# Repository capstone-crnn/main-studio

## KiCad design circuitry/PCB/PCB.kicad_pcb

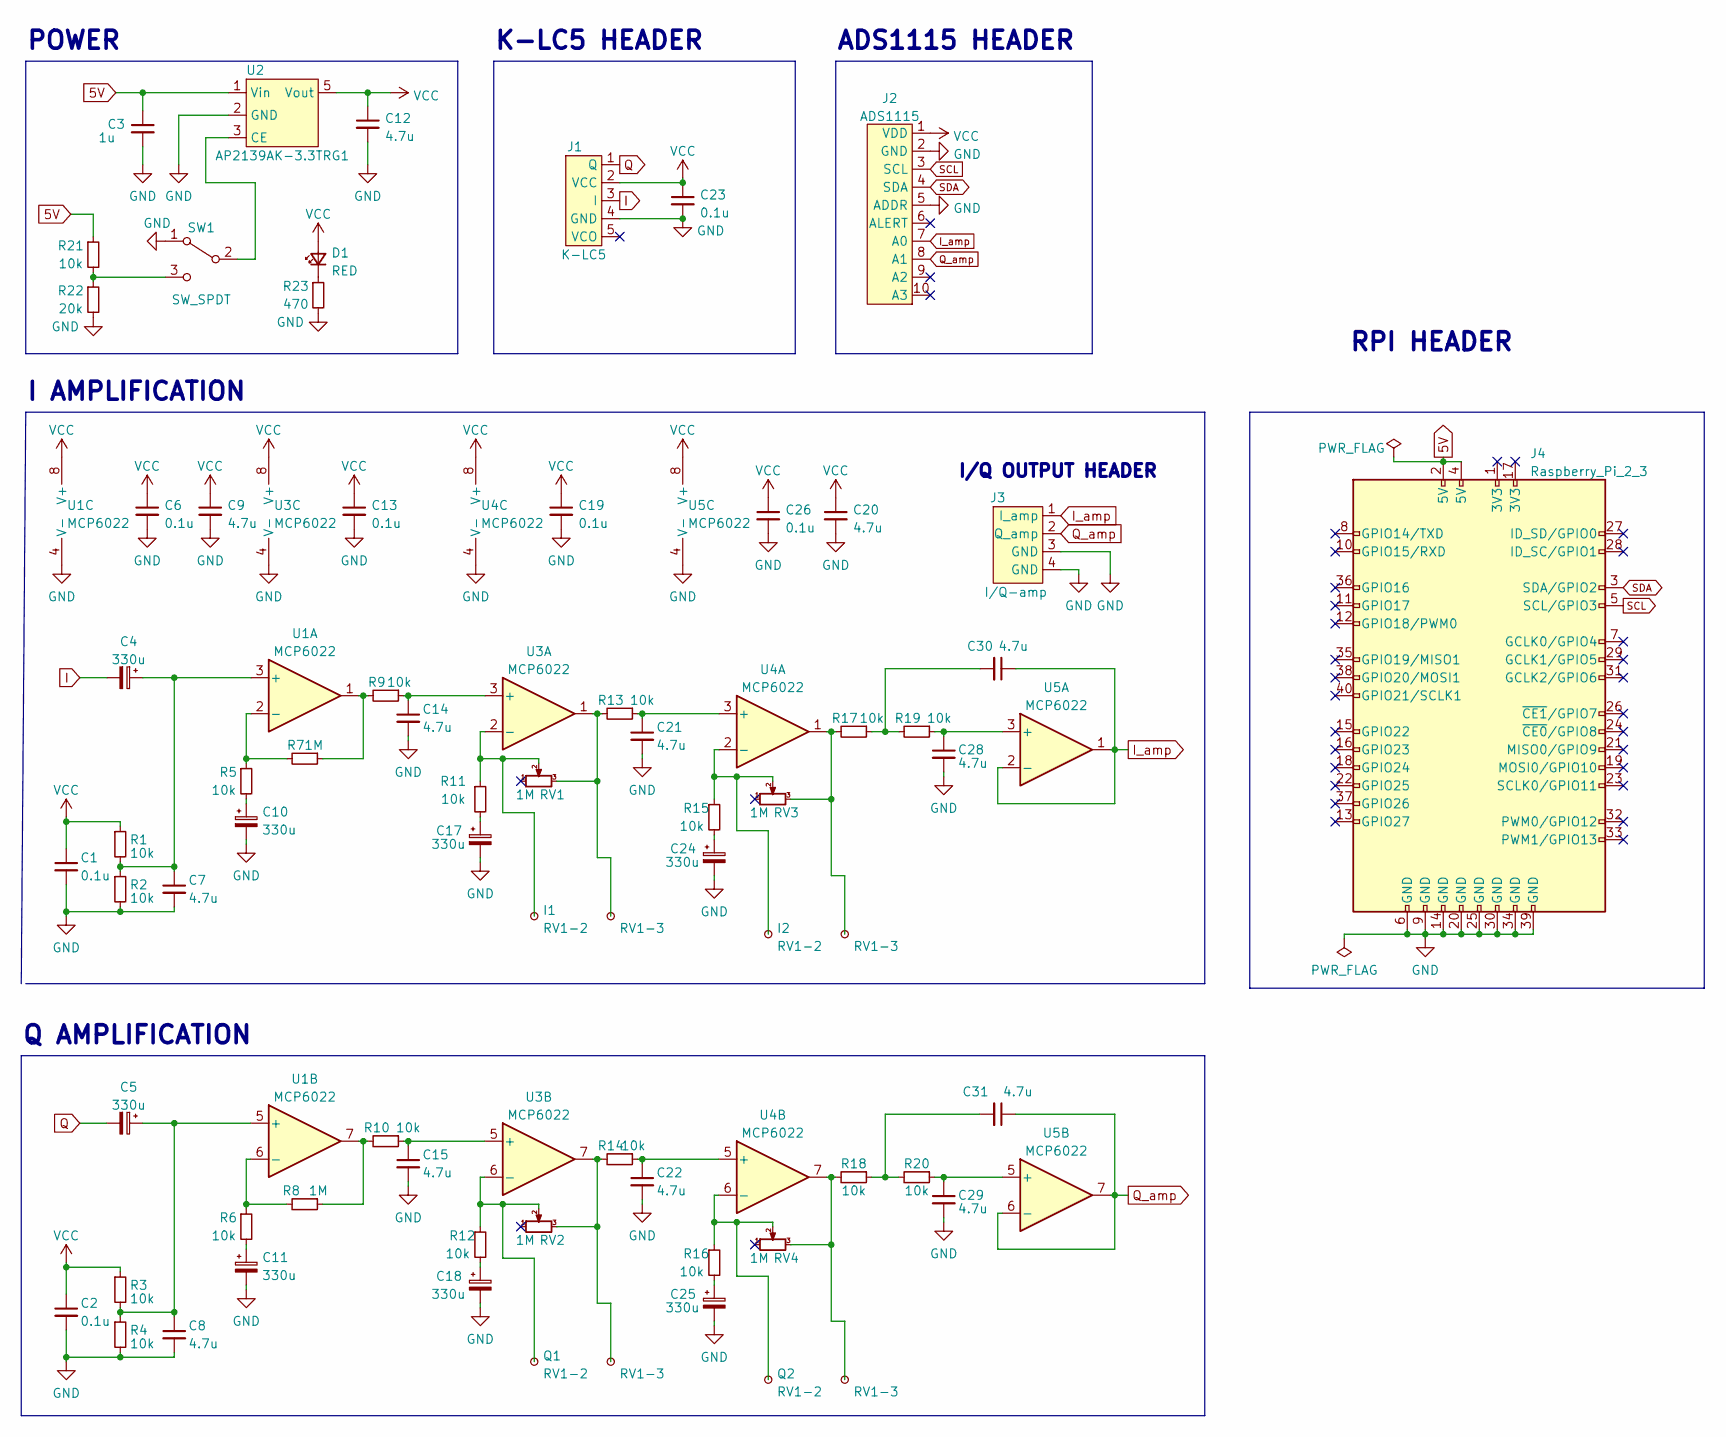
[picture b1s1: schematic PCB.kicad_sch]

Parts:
C1, C2, C6, C13, C19, C23, C26: 0.1u; C_1206_3216Metric_Pad1.33x1.80mm_HandSolder
C3: 1u; C_1206_3216Metric_Pad1.33x1.80mm_HandSolder
C4, C5, C10, C11, C17, C18, C24, C25: 330u; CP_EIA-3528-12_Kemet-T_Pad1.50x2.35mm_HandSolder
C7, C8, C9, C12, C14, C15, C20, C21, C22, C28, C29, C30, C31: 4.7u; C_1206_3216Metric_Pad1.33x1.80mm_HandSolder
D1: RED; LED_1206_3216Metric_Pad1.42x1.75mm_HandSolder
I1, I2: RV1-2; TestPoint_Pad_D2.5mm
J1: K-LC5; PinSocket_1x05_P2.54mm_Vertical
J2: ADS1115; PinSocket_1x10_P2.54mm_Vertical
J3: I/Q-amp; PinSocket_1x02_P2.54mm_Vertical
J4: Raspberry_Pi_2_3; PinSocket_2x20_P2.54mm_Vertical
Q1, Q2: RV1-2; TestPoint_Pad_D2.5mm
R1, R2, R3, R4, R5, R6, R9, R10, R11, R12, R13, R14, R15, R16, R17, R18, R19, R20, R21: 10k; R_1206_3216Metric_Pad1.30x1.75mm_HandSolder
R7, R8: 1M; R_1206_3216Metric_Pad1.30x1.75mm_HandSolder
R22: 20k; R_1206_3216Metric_Pad1.30x1.75mm_HandSolder
R23: 470; R_1206_3216Metric_Pad1.30x1.75mm_HandSolder
RV1, RV2, RV3, RV4: 1M; ST4ETA105
SW1: SW_SPDT; PCM12SMTR
TP3, TP4, TP7, TP8: RV1-3; TestPoint_Pad_D2.5mm
U1, U3, U4, U5: MCP6022; SOIC-8_3.9x4.9mm_P1.27mm
U2: AP2139AK-3.3TRG1; SOT-23-5_HandSoldering

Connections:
5V: C3.1, J4.2 (5V), J4.4 (5V), R21.1, U2.1 (Vin)
GND: C1.2, C2.2, C3.2, C6.2, C7.2, C8.2, C9.2, C10.2, C11.2, C12.2, C13.2, C14.2, C15.2, C17.2, C18.2, C19.2, C20.2, C21.2, C22.2, C23.2, C24.2, C25.2, C26.2, C28.2, C29.2, J1.4 (GND), J2.2 (GND), J2.5 (ADDR), J3.3 (GND), J3.4 (GND), J4.6 (GND), J4.9 (GND), J4.14 (GND), J4.20 (GND), J4.25 (GND), J4.30 (GND), J4.34 (GND), J4.39 (GND), R2.2, R4.2, R22.2, R23.2, SW1.1 (A), U1.4 (V-), U2.2 (GND), U3.4 (V-), U4.4 (V-), U5.4 (V-)
I: C4.2, J1.3 (I)
I_amp: C30.1, J2.7 (A0), J3.1 (Q_amp), U5.1, U5.2 (-)
unnamed: C4.1, C7.1, R1.2, R2.1, U1.3 (+)
unnamed: C5.1, C8.1, R3.2, R4.1, U1.5 (+)
unnamed: C10.1, R5.2
unnamed: C11.1, R6.2
unnamed: C14.1, R9.1, U3.3 (+)
unnamed: C15.1, R10.1, U3.5 (+)
unnamed: C17.1, R11.2
unnamed: C18.1, R12.2
unnamed: C21.1, R13.1, U4.3 (+)
unnamed: C22.1, R14.1, U4.5 (+)
unnamed: C24.1, R15.2
unnamed: C25.1, R16.2
unnamed: C28.1, R19.1, U5.3 (+)
unnamed: C29.1, R20.1, U5.5 (+)
unnamed: C30.2, R17.1, R19.2
unnamed: C31.2, R18.1, R20.2
unnamed: D1.1 (K), R23.1
unnamed: I1.1, R11.1, RV1.2, U3.2 (-)
unnamed: I2.1, R15.1, RV3.2, U4.2 (-)
unnamed: Q1.1, R12.1, RV2.2, U3.6 (-)
unnamed: Q2.1, R16.1, RV4.2, U4.6 (-)
unnamed: R5.1, R7.2, U1.2 (-)
unnamed: R6.1, R8.2, U1.6 (-)
unnamed: R7.1, R9.2, U1.1
unnamed: R8.1, R10.2, U1.7
unnamed: R13.2, RV1.3, TP3.1, U3.1
unnamed: R14.2, RV2.3, TP4.1, U3.7
unnamed: R17.2, RV3.3, TP7.1, U4.1
unnamed: R18.2, RV4.3, TP8.1, U4.7
unnamed: R21.2, R22.1, SW1.3 (C)
unnamed: SW1.2 (B), U2.3 (CE)
Q: C5.2, J1.1 (Q)
Q_amp: C31.1, J2.8 (A1), J3.2 (I_amp), U5.6 (-), U5.7
SCL: J2.3 (SCL), J4.5 (SCL/GPIO3)
SDA: J2.4 (SDA), J4.3 (SDA/GPIO2)
VCC: C1.1, C2.1, C6.1, C9.1, C12.1, C13.1, C19.1, C20.1, C23.1, C26.1, D1.2 (A), J1.2 (VCC), J2.1 (VDD), R1.1, R3.1, U1.8 (V+), U2.5 (Vout), U3.8 (V+), U4.8 (V+), U5.8 (V+)

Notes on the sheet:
I AMPLIFICATION
I/Q OUTPUT HEADER
Q AMPLIFICATION
K-LC5 HEADER
POWER
RPI HEADER
ADS1115 HEADER

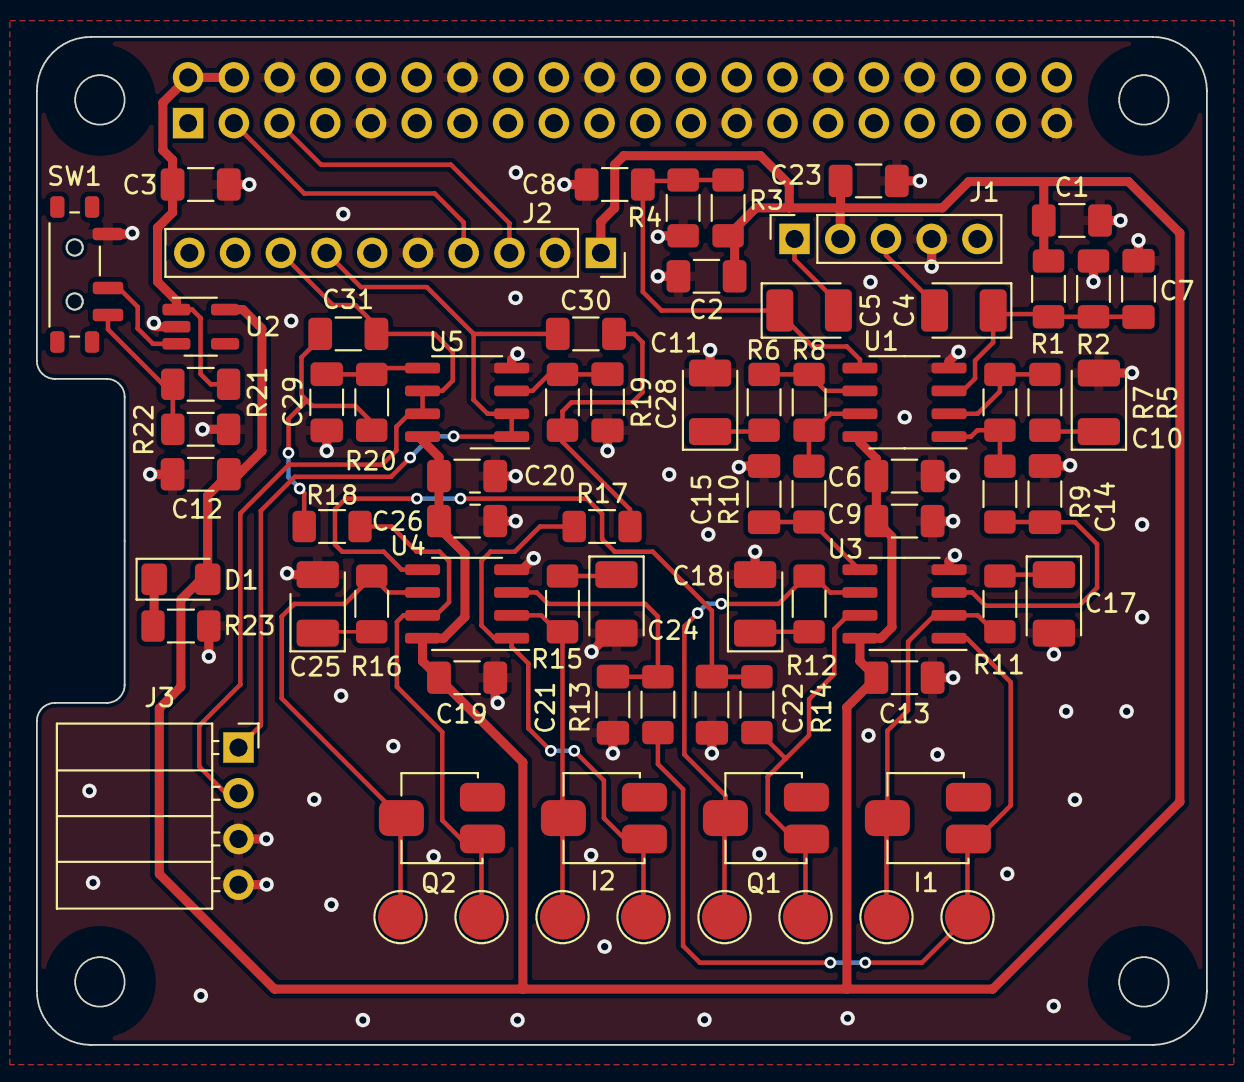
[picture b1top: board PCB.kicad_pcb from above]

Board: 2 copper layers, 65.0 x 56.0 mm, 75 parts (1 on the bottom side), 40 nets.

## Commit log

2022-01-27 [Organization] Creating directories per module
2022-02-18 [Setup] Initial electron, svelte, tailwind app
2022-02-19 [Setup] Added readme with instructions on packing
2022-02-20 [Bug] Fixed routing and SVG linking issues
2022-03-03 [Core] Updated monitor screen, actionbar, statusbar
2022-03-03 [Core] Added Chartjs package
2022-03-10 [Core] Added functionality to read data from file
2022-03-10 [Core] Updated homepage with logo
2022-03-10 [Bug] Updated nav corners with conditional layout
2022-03-10 [Core] Implemented initial search screen
2022-03-11 Initial schematic and symbol design
2022-03-11 Spice simulation
2022-03-12 schematic update
2022-03-12 finish temporary schematic
2022-03-13 initial board layout
2022-03-13 add mounting holes
2022-03-13 layout update
2022-03-16 schematic changes, begin board layout
2022-03-28 [Docs] Minor update to packing instructions
2022-03-28 [Core] Implemented shared memory communication w/ C++ [Core] Implemented live graph of bpm data from shared memory
2022-04-10 [Docs] Updated package name
2022-04-10 [Core] Improved on styles; added shadows, colors, and fonts
2022-04-10 [Core] Added vital signs algo file to electron backend
2022-04-10 [Core] Removed irrelevant error dialog pop ups - removed cursor (for linux) - updated final iteration of data structure from shared mem - added "calibrate" event - tracking two index files; one for w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
2022-04-10 [Core] Finished the Monitor screen implementation - removed placeholder values - implemented "time elapsed" metric - added condition to only show data if human was detected - fixed up styles
2022-04-10 [Core] Finalized Search screen
2022-04-25 just pushing final board design for future reference
